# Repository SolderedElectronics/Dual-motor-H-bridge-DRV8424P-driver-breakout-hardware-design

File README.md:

# Dual motor H-bridge DRV8424P driver breakout Hardware Design

## About the Product

|  |
| :----------------------------------------------------------: |
| [Buy Dual motor H-bridge DRV8424P driver breakout](https://www.solde.red/333160) |

The Dual Motor H-Bridge DRV8424P is a high-performance motor driver module that provides efficient and reliable control for two DC motors or a bipolar stepper motor. It is widely used in robotics, automation, and mechatronics projects where precise motor control is required.

This motor driver module is based on the DRV8424P integrated circuit, which features advanced protection and control capabilities. It supports a wide range of motor voltages, typically from 8V to 45V, and can deliver a continuous output current of up to 2.5A per motor channel. With a peak current of up to 4A, it can handle high-demand applications.

---

## Repository Contents

This repository contains all design files for Dual motor H-bridge DRV8424P driver breakout, organized as follows:

- **`CAD` folder**: Contains KiCAD design files, including:
  - Schematics
  - PCB layout
  - Panel PCB layout
  - Source 3D files in Fusion360, if any
  - All files are sorted by version with a detailed change log.
- **`OUTPUTS` folder**: Includes all production-ready files, such as:
  - Bill of Materials (BOM) and interactive BOM (iBOM)
  - PDF versions of schematics
  - 3D `.step` file of the board
  - 3D-printable models
  - Gerber files for PCB manufacturing
  - Image of the pinout of the board
  - Product image
  - Compliance, legal and generic sales documents

Refer to the `Change Log` in the CAD folder for details about updates between versions.

---

## Learn More About the Product

Beyond the repository, explore the following resources:

### Soldered Verify

The **Soldered Verify** system ensures every board you purchase from Soldered is fully functional. It also provides access to exclusive test data for your product. To get started, find the unique Soldered Verify ID on your product's packaging and enter the ID on the [Soldered Verify page](https://soldered.com/verify/) to access test results and additional product details.

### Soldered Community

Soldered Community is your go-to place for technical support. Our engineers track and answer all questions posted there, and it’s a great space for the maker community. Get answers to your questions and solutions for your challenges at [Soldered Community](https://soldered.com/community).

### solde.red

solde.red is an ultimate URL shortener and information hub. Access it by typing solde.red/ followed by your product SKU, e.g., [solde.red/333000](https://solde.red/333000), to find getting-started guides, datasheets, open-source hardware and software files, certifications, images, pinouts, and more. Read more about the shortener [here](https://solde.red/info/).

---

## Contributing

Contributions are welcome! Here’s how you can get involved:

- Submit pull requests to enhance the design or fix issues.
- Report bugs or problems by opening an issue.

We encourage community collaboration to make this product even better.

---

## About Soldered

[Soldered for Makers](https://soldered.com) specializes in designing and manufacturing electronic products tailored for enthusiasts, ranging from hobbyists to professionals. Our portfolio includes electronic boards, sensors, and actuators that are widely utilized in fields such as microelectronics, mechatronics, robotics, programming, and IoT. Every product we offer is designed in-house and built upon open-source hardware and software platforms. Proudly certified and manufactured within the European Union, our catalog likely includes the product you need for your project.

We complement these products with comprehensive tutorials and manuals, product descriptions, schematics, programming codes, and project examples. Our round-the-clock [customer and technical support](https://soldered.com/community) is available for all our products, irrespective of the sales channel. Soldered’s success and services reflect our maker community’s unwavering [trust](https://www.trustpilot.com/review/soldered.com), for which we are deeply grateful. Join our community and create using Soldered products.

---

## License

All Soldered open-source hardware (OSH) is under The TAPR Open Hardware License. Read more in the LICENSE file located in this repository.

**Disclaimer:**

No warranty - all designs in this repository are distributed in the hope that they will be useful, but without any warranty. They are provided "AS IS", therefore without warranty of any kind, either expressed or implied. The entire quality and performance of what you do with the contents of this repository are your responsibility. In no event Soldered Electronics will be liable for your damages, or losses, including any general, special, incidental, or consequential damage arising out of the use or inability to use the contents of this repository. 

---

## Have fun!

Thank you for your support from your fellow makers at Soldered Electronics.

Happy Making!

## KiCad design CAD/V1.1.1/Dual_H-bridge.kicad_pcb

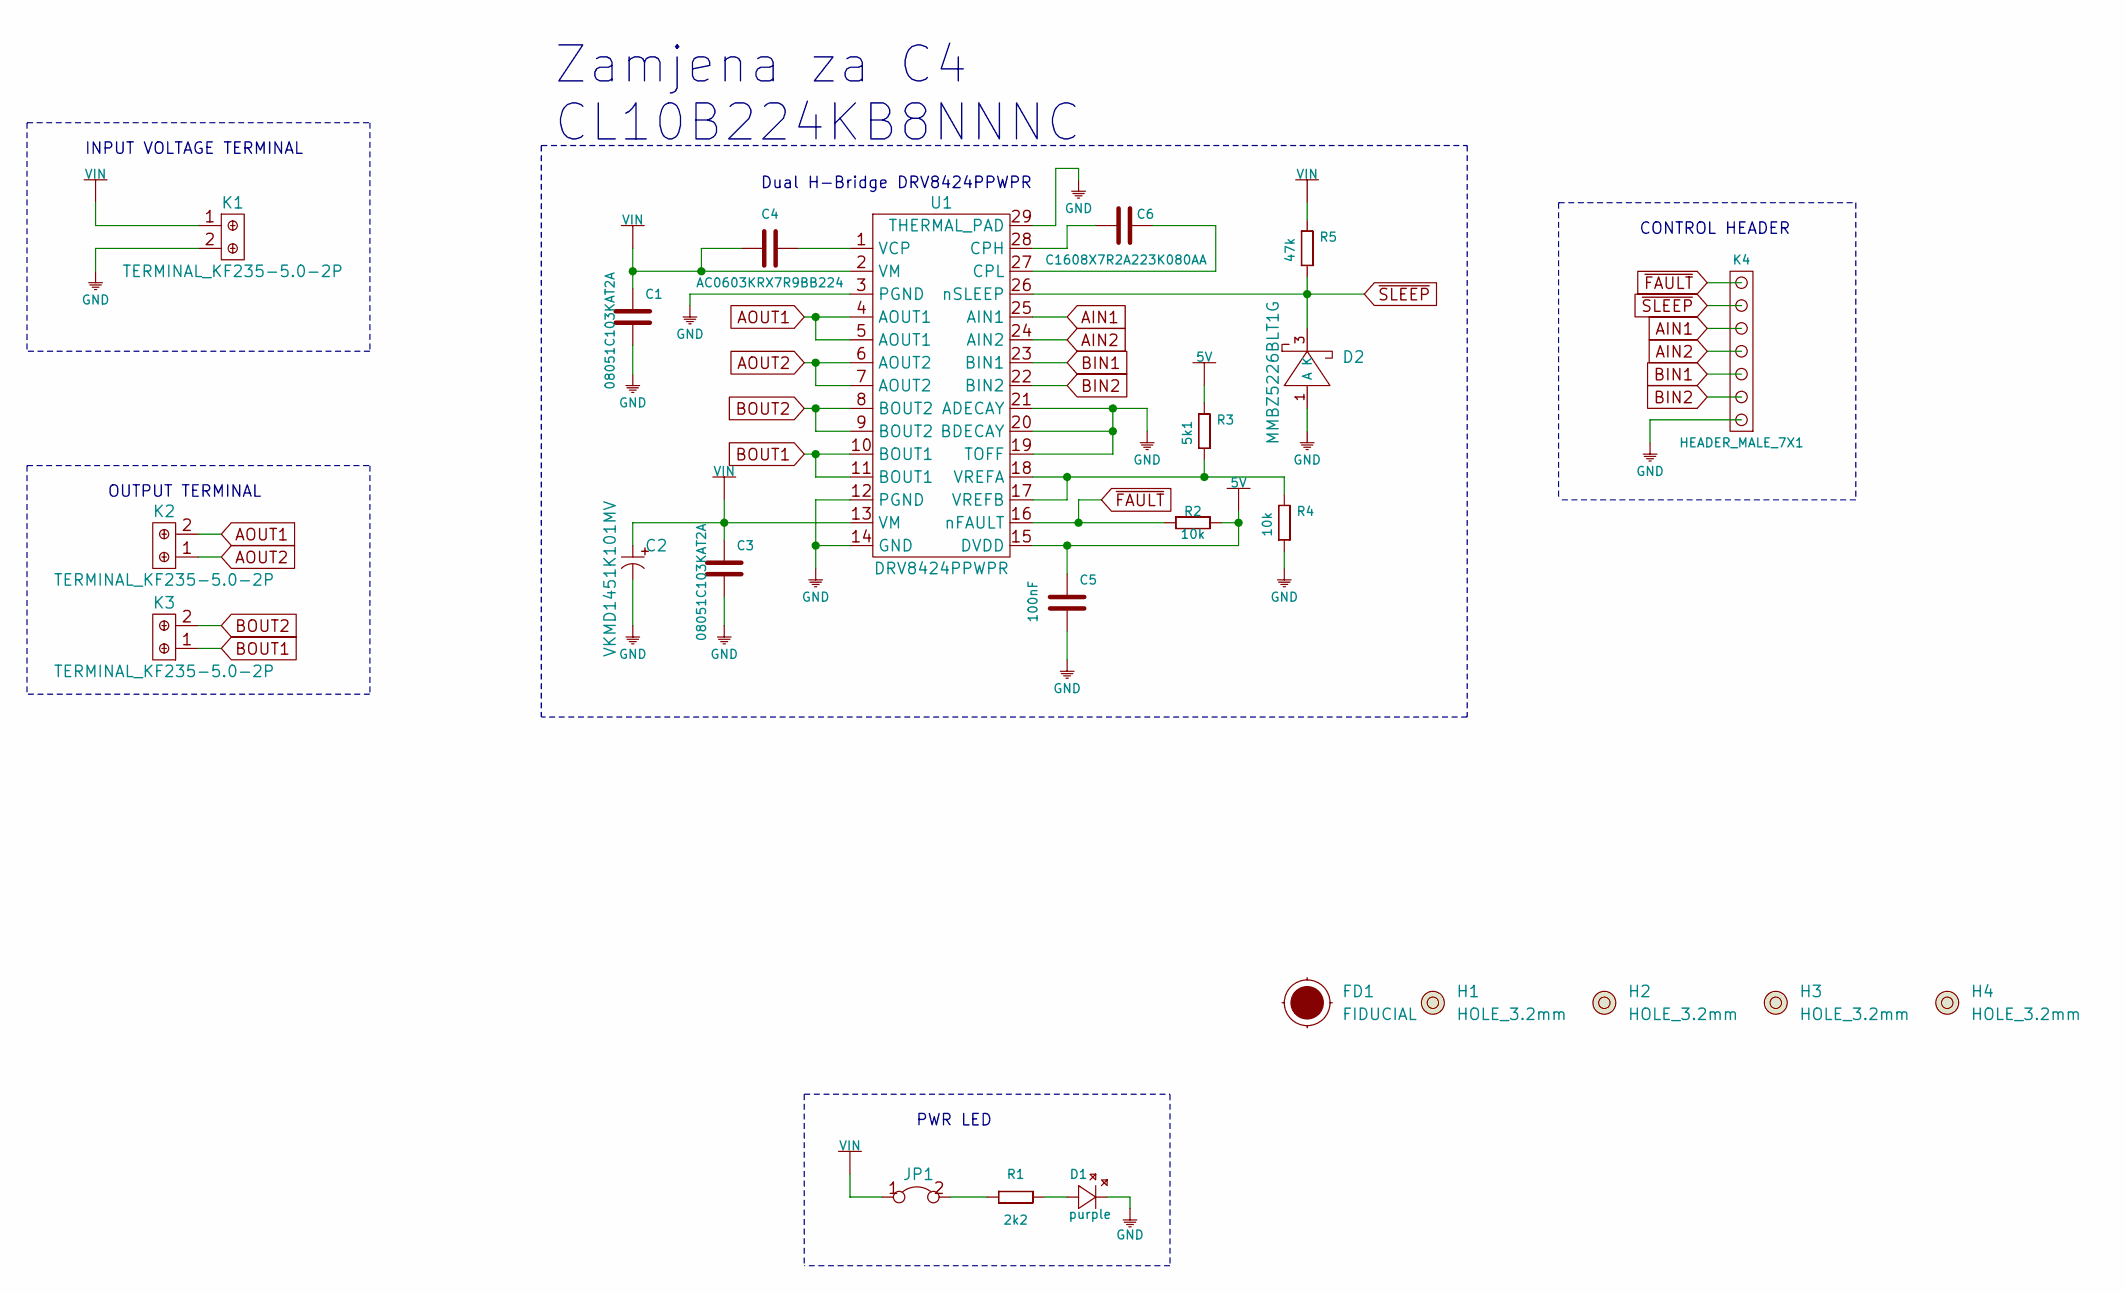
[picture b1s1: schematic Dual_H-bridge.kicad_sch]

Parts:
C1, C3: 08051C103KAT2A; 0805C
C2: VKMD1451K101MV; ELECTROLITIC_CAP_8x8x14.5
C4: AC0603KRX7R9BB224; 0603C
C5: 100nF; 0603C
C6: C1608X7R2A223K080AA; 0603C
D1: purple; 0402LED
D2: MMBZ5226BLT1G; SOT-23-3
FD1: FIDUCIAL; FIDUCIAL_23
H1, H2, H3, H4: HOLE_3.2mm
JP1: SMD-JUMPER-CONNECTED_TRACE_SLODERMASK
K1, K2, K3: TERMINAL_KF235-5.0-2P
K4: HEADER_MALE_7X1
R1: 2k2; 0402R
R2, R4: 10k; 0603R
R3: 5k1; 0603R
R5: 47k; 0603R
U1: DRV8424PPWPR; HTSSOP-28

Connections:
5V: C5.2, R2.2, R3.2, U1.15 (DVDD)
AIN1: K4.5, U1.25 (AIN1)
AIN2: K4.4, U1.24 (AIN2)
AOUT1: K2.2, U1.4 (AOUT1), U1.5 (AOUT1)
AOUT2: K2.1, U1.6 (AOUT2), U1.7 (AOUT2)
BIN1: K4.3, U1.23 (BIN1)
BIN2: K4.2, U1.22 (BIN2)
BOUT1: K3.1, U1.10 (BOUT1), U1.11 (BOUT1)
BOUT2: K3.2, U1.8 (BOUT2), U1.9 (BOUT2)
GND: C1.1, C2.2 (-), C3.1, C5.1, D1.2 (K), D2.1 (A), K1.2, K4.1, R4.1, U1.3 (PGND), U1.12 (PGND), U1.14 (GND), U1.19 (TOFF), U1.20 (BDECAY), U1.21 (ADECAY), U1.29 (THERMAL_PAD)
unnamed: C4.2, U1.1 (VCP)
unnamed: C6.1, U1.27 (CPL)
unnamed: C6.2, U1.28 (CPH)
unnamed: D1.1 (A), R1.2
unnamed: JP1.2, R1.1
unnamed: R3.1, R4.2, U1.17 (VREFB), U1.18 (VREFA)
VIN: C1.2, C2.1 (+), C3.2, C4.1, JP1.1, K1.1, R5.2, U1.2 (VM), U1.13 (VM)
~FAULT: K4.7, R2.1, U1.16 (nFAULT)
~SLEEP: D2.3 (K), K4.6, R5.1, U1.26 (nSLEEP)

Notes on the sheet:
INPUT VOLTAGE TERMINAL
OUTPUT TERMINAL
Zamjena za C4 CL10B224KB8NNNC
PWR LED
Dual H-Bridge DRV8424PPWPR
CONTROL HEADER

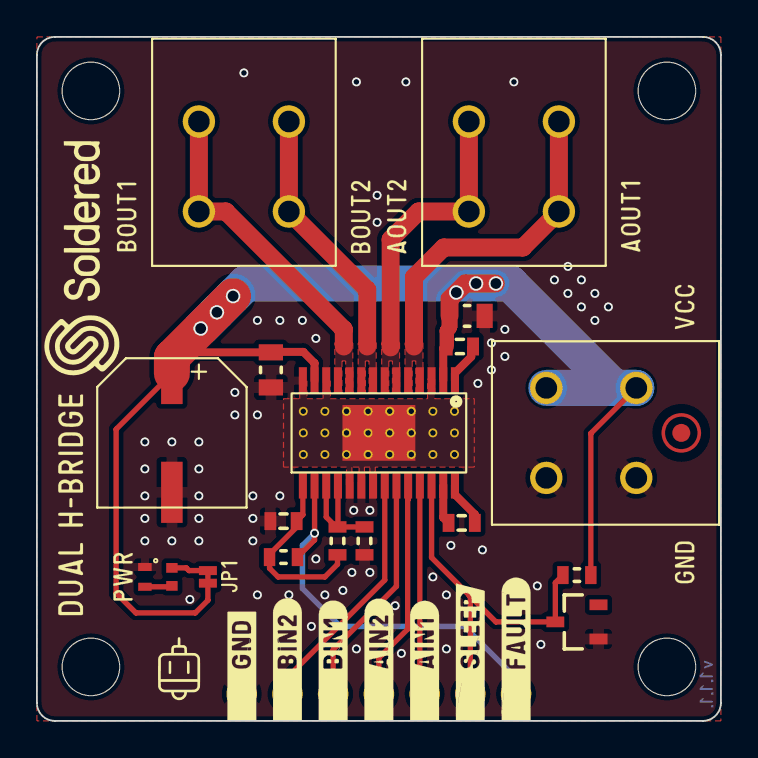
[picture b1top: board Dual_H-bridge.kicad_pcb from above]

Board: 2 copper layers, 38.0 x 38.0 mm, 24 parts (0 on the bottom side), 19 nets.

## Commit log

2022-08-06 Updating open source files.
